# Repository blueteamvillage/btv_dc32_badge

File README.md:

# btv_dc32_badge

BTV DC32 Badge Artifacts

This is a DEFCON Indie badge created for DC32.

This is where all the files for the BTV DC32 Badge will be stored.

This includes code and art and cad and fab files.  All the things.

## File Structure

This is the file structure of this repository

* [/](/README.md) - YOU ARE HERE
* [/art/](./art/) - Artwork and other graphics created by this project
  * [/art/inspiration/](./art/inspiration/) - Art and graphics pulled f6 other sources used as inspiration for this project
  * [/art/fonts/](./art/fonts/) - Fonts used in art and graphics
* [/code/](./code/) - All project related Code / Firmware
* [/docs/](./docs/) - Documentation created by this project including web pages
* [/eda/](./eda/) - Electronic Design Automation files (i.e. KiCad)
  * [/eda/camera_badge/](./eda/camera_badge/) - KiCad 7.x project folder for the camera_badge PCB
* [/reference_parts/](./reference_parts/) - Documentation pulled from other sources related to components
* [/README.md](/README.md) - This File
* [/LICENSE](/LICENSE) - Currently set to MIT

Note: the reference_parts directory is a link to a submodule repository.
To add it use the following cmd after cloning this:
```
git submodule update --init --recursive
```
If adding for the first time (i.e., it is not linked in the remote master) use this:
```
git submodule add https://github.com/gowenrw/reference_parts reference_parts
```
This will make a link to the current commit of that repo.
To update it to a newer commit after its been added use this cmd:
```
git submodule update --remote
```

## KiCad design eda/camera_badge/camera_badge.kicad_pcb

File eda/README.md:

# Electronic Design Automation

This is where all the Electronic Design Automation files for the PCB(s) will be stored.
The EDA used is KiCad 7.x unless otherwise specified.

The KiCad projects have been configured to use local libraries for long term sustainability per the best practices listed [HERE](https://hackaday.com/2017/05/18/kicad-best-practises-library-management/) and elsewhere.

## File Structure

This is the file structure of this repository

* [/](/README.md) - Home
* [/eda](/eda/) - YOU ARE HERE
  * /eda/<project>/ - KiCad project folder for the named project PCB(s)
    * ./3d_models/ - This directory contains footprint 3d model files
    * ./gerber/ - This directory contains gerber formatted files for manufacturing
    * ./lib_fp/ - This directory contains footprint module directories
    * ./lib_sh/ - This directory contains schematic library files
    * ./snapshots/ - This directory contains prints of schematic / cad files and images of preview / final product

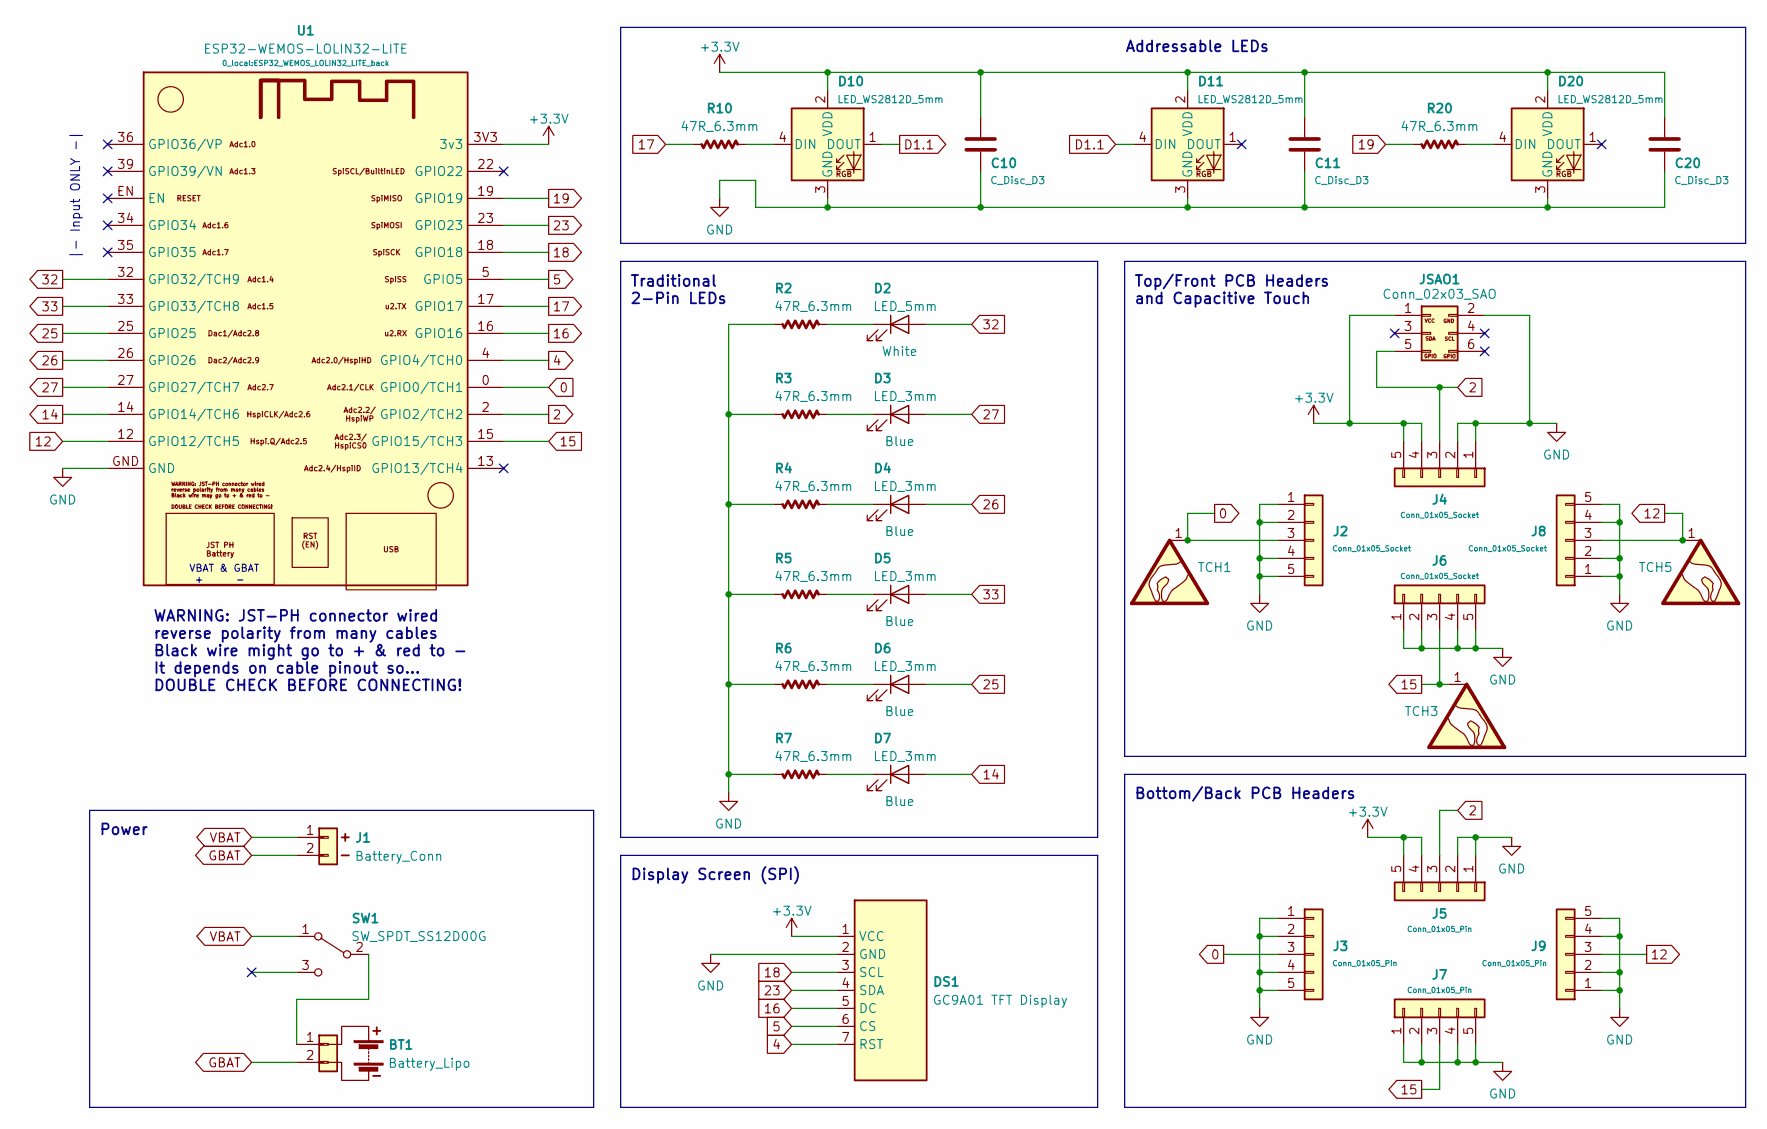
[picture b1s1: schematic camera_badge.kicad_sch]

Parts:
BT1: Battery_Lipo; Battery_Connector_back
C10, C11, C20: C_Disc_D3; C_Disc_D3_back
D2: LED_5mm; LED_D5.0mm-2_back
D3, D4, D5, D6, D7: LED_3mm; LED_D3.0mm-2-std_back
D10, D11, D20: LED_WS2812D_5mm; LED_D5.0mm-4_WS2812D_2024_back
DS1: GC9A01 TFT Display; GC9A01_TFT_Back_Mount
J1: Battery_Conn; Battery_Connector_back
J2, J4, J6, J8: Conn_01x05_Socket; Conn_Pin_Header_Female_Vert_Back_1x05_Pitch2.54mm
J3, J5, J7, J9: Conn_01x05_Pin; Conn_Pin_Header_Male_Vert_Back_1x05_Pitch2.54mm
JSAO1: Conn_02x03_SAO; SAOv169-BADGEv2-2x3_gpio_back
R2, R3, R4, R5, R6, R7, R10, R20: 47R_6.3mm; R_Axial_DIN0207_L6.3_D2.5_P7.62_Horiz_back
SW1: SW_SPDT_SS12D00G; SW_SPDT_Slide_SS12D00G-1P2T_3pin_back
TCH1, TCH3, TCH5: SYM_Touch_lg
U1: ESP32-WEMOS-LOLIN32-LITE; ESP32_WEMOS_LOLIN32_LITE_back

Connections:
0: J2.3, J3.3, TCH1.1, U1.0 (GPIO0/TCH1)
2: J4.3, J5.3, JSAO1.5, U1.2 (GPIO2/TCH2)
4: DS1.7 (RST), U1.4 (GPIO4/TCH0)
5: DS1.6 (CS), U1.5 (GPIO5)
12: J8.3, J9.3, TCH5.1, U1.12 (GPIO12/TCH5)
14: D7.2 (A), U1.14 (GPIO14/TCH6)
15: J6.3, J7.3, TCH3.1, U1.15 (GPIO15/TCH3)
16: DS1.5 (DC), U1.16 (GPIO16)
17: R10.2, U1.17 (GPIO17)
18: DS1.3 (SCL), U1.18 (GPIO18)
19: R20.2, U1.19 (GPIO19)
23: DS1.4 (SDA), U1.23 (GPIO23)
25: D6.2 (A), U1.25 (GPIO25)
26: D4.2 (A), U1.26 (GPIO26)
27: D3.2 (A), U1.27 (GPIO27/TCH7)
32: D2.2 (A), U1.32 (GPIO32/TCH9)
33: D5.2 (A), U1.33 (GPIO33/TCH8)
+3.3V: C10.1, C11.1, C20.1, D10.2 (VDD), D11.2 (VDD), D20.2 (VDD), DS1.1 (VCC), J4.4, J4.5, J5.4, J5.5, JSAO1.1, U1.3V3 (3v3)
D1.1: D10.1 (DOUT), D11.4 (DIN)
GBAT: BT1.2, J1.2
GND: C10.2, C11.2, C20.2, D10.3 (GND), D11.3 (GND), D20.3 (GND), DS1.2 (GND), J2.1, J2.2, J2.4, J2.5, J3.1, J3.2, J3.4, J3.5, J4.1, J4.2, J5.1, J5.2, J6.1, J6.2, J6.4, J6.5, J7.1, J7.2, J7.4, J7.5, J8.1, J8.2, J8.4, J8.5, J9.1, J9.2, J9.4, J9.5, JSAO1.2, R2.2, R3.2, R4.2, R5.2, R6.2, R7.2, U1.GND
unnamed: BT1.1, SW1.2 (B)
unnamed: D2.1 (K), R2.1
unnamed: D3.1 (K), R3.1
unnamed: D4.1 (K), R4.1
unnamed: D5.1 (K), R5.1
unnamed: D6.1 (K), R6.1
unnamed: D7.1 (K), R7.1
unnamed: D10.4 (DIN), R10.1
unnamed: D20.4 (DIN), R20.1
VBAT: J1.1, SW1.1 (A)

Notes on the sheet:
Power
WARNING: JST-PH connector wired reverse polarity from many cables Black wire might go to + & red to - It depends on cable pinout so... DOUBLE CHECK BEFORE CONNECTING!
Display Screen (SPI)
|- Input ONLY -|
Top/Front PCB Headers and Capacitive Touch
VBAT & GBAT + -
Traditional 2-Pin LEDs
Bottom/Back PCB Headers
Addressable LEDs

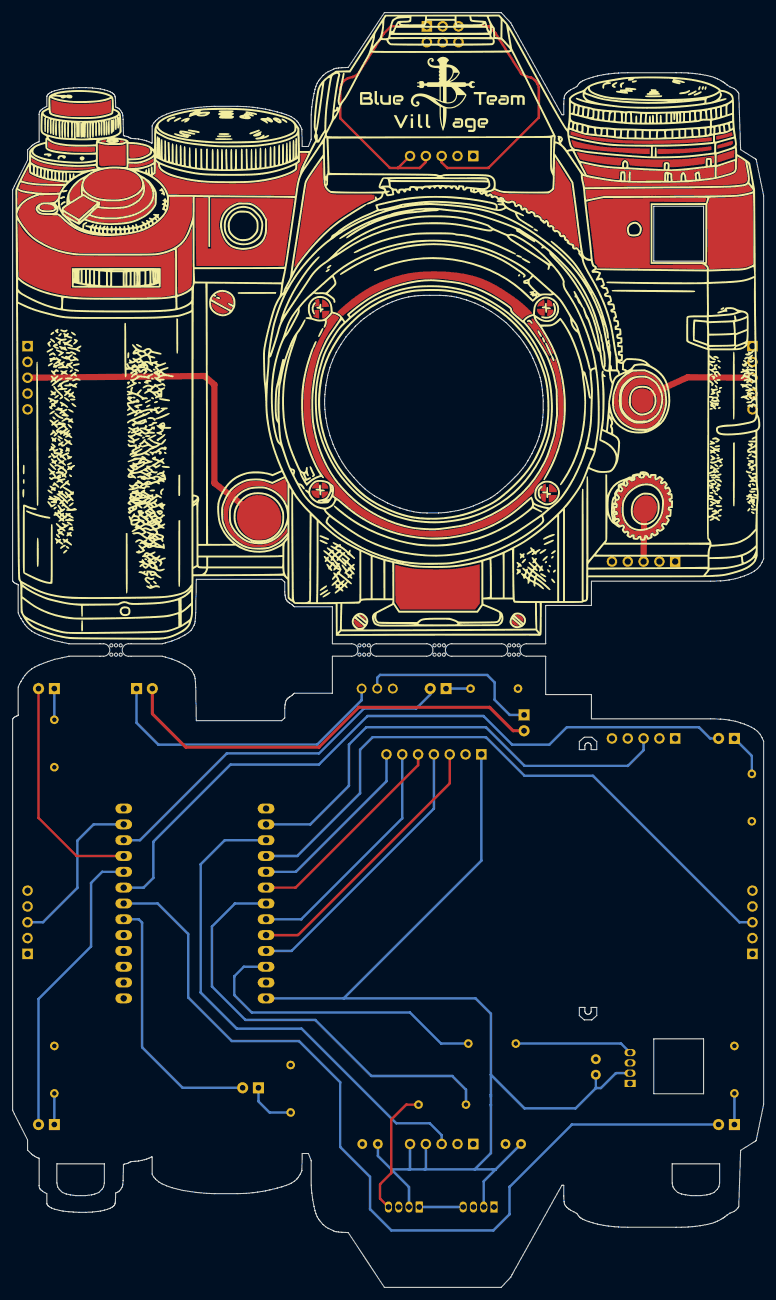
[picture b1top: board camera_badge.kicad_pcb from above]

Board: 2 copper layers, 120.6 x 204.7 mm, 44 parts (0 on the bottom side), 31 nets.

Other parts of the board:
Band_Fastener: Band_Fastener_Hook
Band_Fastener#2: Band_Fastener_Hook
LIPO: Battery_LIPO_103040_silk_back
Lanyard: Lanyard_Hole
Lanyard#2: Lanyard_Hole
badge_bmask01: BMask01; camera_badge_bmask01
badge_copper01: Copper01; camera_badge_copper01
badge_edgecuts: Edge; camera_badge_edgecuts
badge_fmask01: FMask01; camera_badge_fmask01
badge_silk02: Silk02; camera_badge_silk02

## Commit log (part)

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2023-09-28 BTV Gerbers from EasyEDA
2023-12-28 initial badge template
2024-01-11 added some inspiration art
2024-01-18 Create Parts-List
2024-01-18 Rename Parts-List to Parts-List.md
2024-01-20 added part links
2024-01-20 screen links
2024-02-06 screen poc code
2024-02-06 screen testing
2024-02-07 better screen poc 02
2024-02-16 eda updates
2024-02-20 started art
2024-02-20 eda conversion to KiCad v7
2024-02-21 art and eda updates
2024-02-21 badge eda updates
2024-02-22 eda update
2024-02-27 Added a CLI uploader for Mac users
2024-03-04 updated parts list
2024-03-13 made badge wider
2024-03-14 art and fotprint and pcb updates
2024-03-18 added ESP32 Wemos Lolin32 Lite schem footprints 3D
2024-03-18 added reference_parts submodule
2024-03-22 updated arduino version and recompiled code
2024-03-22 code compile script update
2024-03-25 footprint and schem updates
2024-03-25 footprint and schematic updates
2024-03-26 schematic update
2024-03-27 pcb work
2024-03-27 pcb updates
2024-03-27 pcb trace work
2024-04-02 prototype completed
2024-04-11 test code for prototype
2024-04-12 pcb rev2 updates
2024-04-18 second prototype done
2024-04-20 push initial brains of the deauth sniffer
2024-04-29 added deauth sniff to camera_badge_rev01 code
2024-05-06 Component BOM completed
2024-05-08 code update
2024-05-12 display on the screen and restructure serial output
2024-05-12 code format
2024-07-18 pushed main screen idle effect.
2024-07-18 push camera shutter effect
2024-07-21 code update touch logic and battchg-off
2024-07-22 push wof on tch03
2024-07-22 remove unused 16-bit color define
2024-07-25 docs cleanup
2024-07-28 Create CNAME
2024-08-05 Adding Assembly Instructions
2024-08-05 Update BadgeInstructions.md for typos fixes
2024-08-05 Add instruction images
2024-08-05 Update index.md to link to instructions page
